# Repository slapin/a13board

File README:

Copyright (C) 2013 Sergey Lapin

These schematics and PCB layout are free: you can redistribute it
and/or modify it under the terms of the GNU General Public License
as published by the Free Software Foundation, either version 3
of the License, or (at your option) any later version.

This schematic and PCB layout are distributed in the hope that these
will be useful, but WITHOUT ANY WARRANTY; without even the implied
warranty of MERCHANTABILITY or FITNESS FOR A PARTICULAR PURPOSE.
See the GNU General Public License for more details.

You should have received a copy of the GNU General Public License
along with this program.  If not, see <http://www.gnu.org/licenses/>.

Please note, that this license is only for schematics and board layout,
and symbol libraries.
I don't know, and I don't want to know of any patent issues you can get
into using this design. Good luck.

Also, `sexpdata` is licensed under the terms of the BSD 2-Clause License.
See the source code for more information.

Symbol for Allwinner A13 was taken from Olimex PCB for OLinuXino,
and is subject to their license and permissions.
See https://github.com/OLIMEX/OLINUXINO

S.

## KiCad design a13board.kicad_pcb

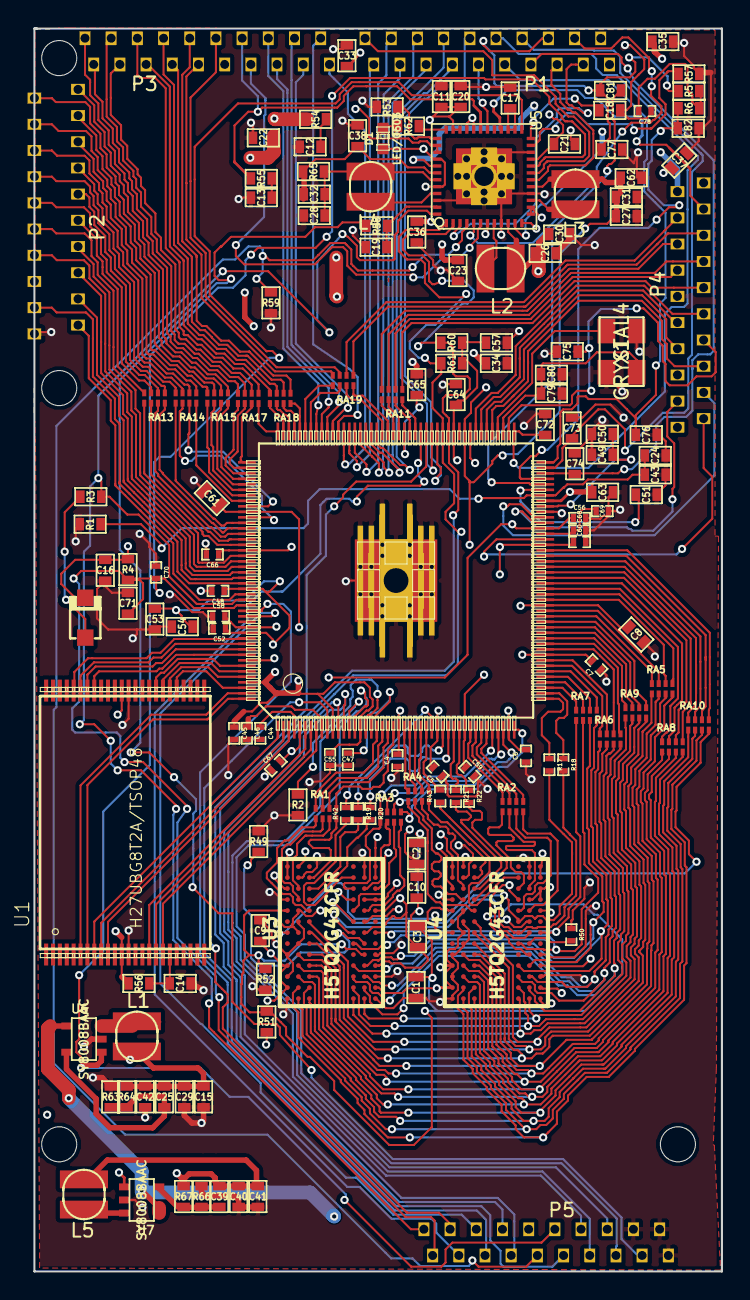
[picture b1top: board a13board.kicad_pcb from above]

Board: 4 copper layers, 50.0 x 90.4 mm, 156 parts (0 on the bottom side), 271 nets.

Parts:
1PIN, 1PIN#2, 1PIN#3, 1PIN#4: P***; 1pin
C1, C2, C3: 100nF; SM0603_Capa
C4, C5, C6, C7, C45, C47, C52, C55, C56, C60, C67, C69: 100nF; SM0402
C8, C9, C10, C15, C43, C50, C54, C57, C64, C65, C71, C81: 100nF; SM0603A
C11, C12, C13, C20, C21, C22, C23, C24, C26, C27, C28, C33, C34, C35, C36, C37, C38, C49, C53, C62, C82: 10uF/6.3V; SM0603A
C14: NA(100nF); SM0603A
C16: NA(22uF/6.3V); SM0603A
C17, C18, C32, C51: 1uF; SM0603A
C19, C30, C31, C72, C73, C74, C75, C76: 1nF; SM0603A
C25: 47pF; SM0603A
C29, C40, C41, C42, C63: 22uF/6.3V; SM0603A
C39: 22pF; SM0603A
C44, C58, C66: 22uF/6.3V; SM0402
C46, C48, C59, C68, C78: 10uF/6.3V; SM0402
C61: 100nF; SM0603
C70: 1uF; SM0402
C77: 3.3nF; SM0603A
C79, C80: 33pF; SM0603A
D1: LED/0603; LED-0603
D2: 1N5819(S4SOD-123); SOD123
L1, L2, L3, L4, L5: 2.2uH/1.5A/DCR<0.1R/CD32; CD32
P1, P2, P3, P4, P5: CONN_20; CONN20-1.27zzz
R1, R57: 200k/1%; SM0603A
R2, R49, R53: 240R/1%; SM0603A
R3, R4: 47k; SM0603A
R5, R6, R58, R59, R60, R61, R62: 2.2k; SM0603A
R17, R18, R19, R20, R21, R22, R42, R43: 22R; SM0402
R50: 240R/1%; SM0402
R51, R52: 2k/1%; SM0603A
R54, R55: 1R; SM0603A
R56: NA(10k); SM0603A
R63: 22k/1%; SM0603A
R64: 100k/1%; SM0603A
R65: 0.03R/1%; SM0603A
R66: 3.3k/1%; SM0603A
R67: 4.99k/1%; SM0603A
RA1, RA2, RA3, RA4, RA5, RA6, RA7, RA8, RA9, RA10, RA11, RA13, RA14, RA15, RA17, RA18, RA19: RA4X0402; RN4x0402
U1: H27UBG8T2A/TSOP48; TSOP48
U2: A13; allwinner_a13-OLIMEX_IC_TQFP176
U3, U4: H5TQ2G43CFR; BGA78
U5: OLIMEX_IC_AXP209; QFN48+1
U6, U7: SY8008BAAC; SOT23-5
X1: CRYSTAL4; C5032

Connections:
5V_EXT: P3.9, R54.2, U5.32, U5.33
5V_OTG: P3.8, R55.2, U5.31
+3.3V: C15.1, C16.1, C25.2, C29.2, C42.2, C56.2, C57.2, C58.1, C61.1, C64.1, C67.1, D2.1, L1.2, P4.1, R4.1, R56.1, R60.1, R61.1, R64.2, U1.12, U1.37, U2.5, U2.76, U2.97, U2.100, U2.142, U2.163
+BATT: P1.20, U5.38, U5.39
/DRAM/CPU_A0: RA5.1, U2.64
/DRAM/CPU_A1: RA6.3, U2.52
/DRAM/CPU_A2: RA8.3, U2.66
/DRAM/CPU_A3: RA8.4, U2.65
/DRAM/CPU_A4: RA6.4, U2.51
/DRAM/CPU_A5: RA8.2, U2.67
/DRAM/CPU_A6: RA6.2, U2.54
/DRAM/CPU_A7: RA10.2, U2.71
/DRAM/CPU_A8: RA6.1, U2.55
/DRAM/CPU_A9: RA10.4, U2.69
/DRAM/CPU_A10: RA7.3, U2.48
/DRAM/CPU_A11: RA9.4, U2.56
/DRAM/CPU_A12: RA7.1, U2.50
/DRAM/CPU_A13: RA8.1, U2.68
/DRAM/CPU_A14: RA9.3, U2.57
/DRAM/CPU_BA0: RA5.2, U2.63
/DRAM/CPU_BA1: RA7.2, U2.49
/DRAM/CPU_BA2: RA5.3, U2.61
/DRAM/CPU_CAS: RA9.1, U2.59
/DRAM/CPU_CK: R17.2, U2.45
/DRAM/CPU_CKE: RA7.4, U2.47
/DRAM/CPU_CK_N: R18.2, U2.46
/DRAM/CPU_D0: RA1.1, U2.22
/DRAM/CPU_D1: RA3.4, U2.40
/DRAM/CPU_D2: RA1.2, U2.21
/DRAM/CPU_D3: RA3.3, U2.41
/DRAM/CPU_D4: RA1.4, U2.19
/DRAM/CPU_D5: RA3.1, U2.44
/DRAM/CPU_D6: RA1.3, U2.20
/DRAM/CPU_D7: RA3.2, U2.42
/DRAM/CPU_D8: RA2.3, U2.37
/DRAM/CPU_D9: RA4.3, U2.25
/DRAM/CPU_D10: RA2.1, U2.39
/DRAM/CPU_D11: RA4.4, U2.24
/DRAM/CPU_D12: RA2.4, U2.36
/DRAM/CPU_D13: RA4.2, U2.26
/DRAM/CPU_D14: RA2.2, U2.38
/DRAM/CPU_D15: RA4.1, U2.27
/DRAM/CPU_DM0: R42.1, U2.29
/DRAM/CPU_DM1: R43.1, U2.28
/DRAM/CPU_DQS0: R19.2, U2.31
/DRAM/CPU_DQS0_N: R20.2, U2.32
/DRAM/CPU_DQS1: R21.2, U2.33
/DRAM/CPU_DQS1_N: R22.2, U2.34
/DRAM/CPU_MEMRST: RA10.3, U2.70
/DRAM/CPU_ODT: RA10.1, U2.72
/DRAM/CPU_RAS: RA9.2, U2.58
/DRAM/CPU_WE: RA5.4, U2.60
/DRAM/DDR3_A0: RA5.8, U3.K3, U4.K3
/DRAM/DDR3_A1: RA6.6, U3.L7, U4.L7
/DRAM/DDR3_A2: RA8.6, U3.L3, U4.L3
/DRAM/DDR3_A3: RA8.5, U3.K2, U4.K2
/DRAM/DDR3_A4: RA6.5, U3.L8, U4.L8
/DRAM/DDR3_A5: RA8.7, U3.L2, U4.L2
/DRAM/DDR3_A6: RA6.7, U3.M8, U4.M8
/DRAM/DDR3_A7: RA10.7, U3.M2, U4.M2
/DRAM/DDR3_A8: RA6.8, U3.N8, U4.N8
/DRAM/DDR3_A9: RA10.5, U3.M3, U4.M3
/DRAM/DDR3_A10: RA7.6, U3.H7, U4.H7
/DRAM/DDR3_A11: RA9.5, U3.M7, U4.M7
/DRAM/DDR3_A12: RA7.8, U3.K7, U4.K7
/DRAM/DDR3_A13: RA8.8, U3.N3, U4.N3
/DRAM/DDR3_A14: RA9.6, U3.N7, U4.N7
/DRAM/DDR3_BA0: RA5.7, U3.J2, U4.J2
/DRAM/DDR3_BA1: RA7.7, U3.K8, U4.K8
/DRAM/DDR3_BA2: RA5.6, U3.J3, U4.J3
/DRAM/DDR3_CAS: RA9.8, U3.G3, U4.G3
/DRAM/DDR3_CK: R17.1, U3.F7, U4.F7
/DRAM/DDR3_CKE: RA7.5, U3.G9, U4.G9
/DRAM/DDR3_CK_N: R18.1, U3.G7, U4.G7
/DRAM/DDR3_D0: RA1.8, U3.B3
/DRAM/DDR3_D1: RA3.5, U3.C7
/DRAM/DDR3_D2: RA1.7, U3.C2
/DRAM/DDR3_D3: RA3.6, U3.C8
/DRAM/DDR3_D4: RA1.5, U3.E3
/DRAM/DDR3_D5: RA3.8, U3.E8
/DRAM/DDR3_D6: RA1.6, U3.D2
/DRAM/DDR3_D7: RA3.7, U3.E7
/DRAM/DDR3_D8: RA2.6, U4.C8
/DRAM/DDR3_D9: RA4.6, U4.D2
/DRAM/DDR3_D10: RA2.8, U4.E8
/DRAM/DDR3_D11: RA4.5, U4.E3
/DRAM/DDR3_D12: RA2.5, U4.C7
/DRAM/DDR3_D13: RA4.7, U4.C2
/DRAM/DDR3_D14: RA2.7, U4.E7
/DRAM/DDR3_D15: RA4.8, U4.B3
/DRAM/DDR3_DM0: R42.2, U3.B7
/DRAM/DDR3_DM1: R43.2, U4.B7
/DRAM/DDR3_DQS0: R19.1, U3.C3
/DRAM/DDR3_DQS0_N: R20.1, U3.D3
/DRAM/DDR3_DQS1: R21.1, U4.C3
/DRAM/DDR3_DQS1_N: R22.1, U4.D3
/DRAM/DDR3_ODT: RA10.8, U3.G1, U4.G1
/DRAM/DDR3_RAS: RA9.7, U3.F3, U4.F3
/DRAM/DDR3_RST: RA10.6, U3.N2, U4.N2
/DRAM/DDR3_WE: RA5.5, U3.H3, U4.H3
/NAND/NALE: U1.17, U2.7
/NAND/NAND_WP: C14.1, R56.2, U1.19
/NAND/NCE0: U1.9, U2.2
/NAND/NCE1: U1.10, U2.3
/NAND/NCLE: U1.16, U2.6
/NAND/NDQ0: U1.29, U2.174
/NAND/NDQ1: U1.30, U2.172
/NAND/NDQ2: U1.31, U2.171
/NAND/NDQ3: U1.32, U2.170
/NAND/NDQ4: U1.41, U2.168
/NAND/NDQ5: U1.42, U2.167
/NAND/NDQ6: U1.43, U2.166
/NAND/NDQ7: U1.44, U2.165
/NAND/NRB0: U1.7, U2.176
/NAND/NRB1: U1.6, U2.175
/NAND/NRE: U1.8, U2.1
/NAND/NWE: U1.18, U2.8
/power/VDD_CPU: C26.2, C30.2, C44.2, C45.2, C46.2, C47.2, C48.2, C52.2, C53.2, C54.2, L2.2, U2.4, U2.9, U2.11, U2.16, U2.156, U2.164, U2.169, U2.173, U5.10
/power/VDD_INT: C27.2, C31.2, C59.2, C60.2, C62.2, C65.2, C66.2, L3.2, U2.35, U2.73, U2.98, U2.109, U2.149, U5.17
BACKUP: P1.10, U5.30
EXTEN: P5.10, U5.20, U6.1
GND: C1.2, C2.2, C4.2, C5.2, C6.2, C7.2, C8.2, C9.2, C10.2, C11.1, C12.1, C13.1, C14.2, C15.2, C16.2, C17.1, C18.1, C19.1, C20.1, C21.2, C22.2, C23.2, C24.1, C26.1, C27.1, C28.1, C29.1, C30.1, C31.1, C33.2, C34.2, C35.2, C36.2, C37.2, C38.1, C40.1, C41.1, C42.1, C43.1, C44.1, C45.1, C46.1, C47.1, C48.1, C49.1, C50.1, C51.2, C52.1, C53.1, C54.1, C55.2, C56.1, C57.1, C58.2, C59.1, C60.1, C61.2, C62.1, C63.2, C64.2, C65.1, C66.1, C67.2, C68.1, C69.1, C70.2, C71.2, C72.2, C73.2, C74.2, C75.2, C76.2, C77.2, C78.2, C79.1, C80.1, C82.2, P2.1, P4.11, P5.1, P5.2, P5.4, R1.1, R2.2, R49.2, R50.2, R52.2, R53.1, R57.1, R59.1, R63.1, R66.1, U1.13, U1.36, U2.79, U2.GND, U3.A1, U3.A8, U3.B1, U3.B2, U3.B8, U3.C9, U3.D1, U3.D8, U3.D9, U3.F2, U3.F8, U3.H2, U3.J1, U3.J9, U3.L1, U3.L9, U3.N1, U3.N9, U4.A1, U4.A8, U4.B1, U4.B2, U4.B8, U4.C9, U4.D1, U4.D8, U4.D9, U4.F2, U4.F8, U4.H2, U4.J1, U4.J9, U4.L1, U4.L9, U4.N1, U4.N9, U5.9, U5.16, U5.22, U5.46, U5.GND, U6.2, U7.2, X1.2, X1.4
HPCOM: P4.3, U2.77
HPOUTL: P4.2, U2.74
HPOUTR: P4.4, U2.78
IPSOUT: C11.2, C20.2, C21.1, C22.1, C23.1, C36.1, D1.1, P4.5, P5.12, U5.7, U5.13, U5.14, U5.21, U5.34, U5.35, U5.40, U5.44, U6.4, U7.4
LDO4_3V3_200MA: C37.1, P4.20, U5.11
LRADC: C74.1, P1.14, U2.86
MIC: C77.1, C81.1, P1.15, R5.1
unnamed: R50.1, U4.H8
unnamed: R49.1, U3.H8
unnamed: C1.1, C2.1, C3.2, C10.1, R51.2, R52.1, U3.E1, U3.J8, U4.E1, U4.J8
unnamed: L1.1, U6.3
unnamed: L5.1, U7.3
unnamed: C25.1, R63.2, R64.1, U6.5
unnamed: C39.1, R66.2, R67.1, U7.5
unnamed: C68.2, C69.2, U2.75
unnamed: D2.2, R3.1
unnamed: C32.1, C38.2, R65.2, U5.42
unnamed: C49.2, C50.2, U2.80
unnamed: C24.2, C43.2, R1.2, U2.82
unnamed: R2.1, U2.17
unnamed: C51.1, U2.83
unnamed: L3.1, U5.15
unnamed: L4.1, U5.45
unnamed: C17.2, U5.26, U5.27
unnamed: R53.2, U5.37
unnamed: L2.1, U5.8
unnamed: R62.2, U5.36
unnamed: C12.2, R54.1
unnamed: C13.2, R55.1
unnamed: D1.2, R62.1
unnamed: R57.2, U5.23
unnamed: C18.2, U5.24
unnamed: C28.2, C32.2, L4.2, R65.1, U5.43
unnamed: C19.2, R58.2, U5.47
unnamed: RA11.1, U2.111
unnamed: RA14.3, U2.141
unnamed: RA14.2, U2.143
unnamed: RA14.1, U2.144
unnamed: RA13.4, U2.145
unnamed: RA13.3, U2.146
unnamed: RA13.2, U2.147
unnamed: RA13.1, U2.148
unnamed: RA14.4, U2.140
unnamed: RA11.2, U2.110
unnamed: RA19.1, U2.127
unnamed: RA19.2, U2.126
unnamed: RA15.1, U2.139
unnamed: RA18.4, U2.128
unnamed: RA18.3, U2.129
unnamed: RA18.2, U2.130
unnamed: RA18.1, U2.131
unnamed: RA17.4, U2.132
unnamed: RA17.3, U2.133
unnamed: RA17.2, U2.134
unnamed: RA17.1, U2.135
unnamed: RA15.4, U2.136
unnamed: RA15.3, U2.137
unnamed: RA15.2, U2.138
unnamed: C79.2, C80.2, U2.91, X1.1
unnamed: RA19.3, U2.113
unnamed: RA11.4, U2.107
unnamed: RA11.3, U2.108
unnamed: RA19.4, U2.112
unnamed: C81.2, U2.84
unnamed: C78.1, R5.2, R6.1
unnamed: C82.1, R6.2, U2.85
unnamed: U2.92, X1.3
NMI_N: P5.20, R3.2, U2.158, U5.48
PB2: P1.9, U2.103
PB3: P2.9, U2.150
PB4: P1.8, U2.104
PB10: P5.9, U2.10
PB15: P5.18, U2.105
PB16: P5.17, U2.106
PB17: P5.16, U2.161
PB18: P5.15, U2.160
PD2: P2.10, RA13.8
PD3: P2.11, RA13.7
PD4: P2.12, RA13.6
PD5: P2.13, RA13.5
PD6: P2.14, RA14.8
PD7: P2.15, RA14.7
PD10: P2.16, RA14.6
PD11: P2.17, RA14.5
PD12: P2.18, RA15.8
PD13: P2.19, RA15.7
PD14: P2.20, RA15.6
PD15: P3.20, RA15.5
PD18: P3.19, RA17.8
PD19: P3.18, RA17.7
PD20: P3.17, RA17.6
PD21: P3.16, RA17.5
PD22: P3.15, RA18.8
PD23: P3.14, RA18.7
PD24: P3.13, RA18.6
PD25: P3.12, RA18.5
PD26: P3.11, RA19.8
PD27: P3.10, RA19.7
PE0: P1.7, U2.114
PE1: P1.6, U2.115
PE2: P1.5, U2.116
PE3: P1.4, U2.117
PE4: P1.3, U2.118
PE5: P1.2, U2.119
PE6: P3.1, U2.120
PE7: P3.2, U2.121
PE8: P3.3, U2.122
PE9: P3.4, U2.123
PE10: P3.5, U2.124
PE11: P3.6, U2.125
PG0: P2.3, U2.155
PG1: P2.4, U2.154
PG2: P2.6, U2.153
PG3: P2.7, U2.152
PG4: P2.8, U2.151
PG9: P5.8, U2.12
PG10: P5.7, U2.13
PG11: P5.6, U2.14
PG12: P5.5, U2.15
PIN0: P1.1, U5.19
PIN1: P1.16, U5.18
PIN2: P1.17, U5.5
PIN3: P1.18, U5.3
PWR_BUT: P5.3, R58.1
RESET: C70.1, C71.1, P5.19, R4.2, U2.159, U5.25
RESET_SW2: P5.11, R59.2, U5.4
SDC0_CLK: P4.14, RA11.7
SDC0_CMD: P4.15, RA11.8
SDC0_D0: P4.13, RA11.6
SDC0_D1: P4.12, RA11.5
SDC0_D2: P4.17, RA19.6
SDC0_D3: P4.16, RA19.5
SVREF: C55.1, U2.18
TPX1: C72.1, P1.11, U2.89
TPX2: C73.1, P1.13, U2.87
TPY1: C75.1, P4.8, U2.90
TPY2: C76.1, P1.12, U2.88
TWI0_SCK: P5.14, R60.2, U2.101, U5.2
TWI0_SDA: P5.13, R61.2, U2.102, U5.1
UBOOT: P2.2, U2.157
USB0-DRV: P3.7, U5.6
USB_UDM0: P4.6, U2.93
USB_UDM1: P4.9, U2.95
USB_UDP0: P4.7, U2.94
USB_UDP1: P4.10, U2.96
VDD_RTC: C33.1, P4.18, U5.28
VMEM: C3.1, C4.1, C5.1, C6.1, C7.1, C8.1, C9.1, C39.2, C40.2, C41.2, L5.2, R51.1, R67.2, U2.23, U2.30, U2.43, U2.53, U2.62, U3.A2, U3.A9, U3.B9, U3.C1, U3.D7, U3.E2, U3.E9, U3.G2, U3.G8, U3.K1, U3.K9, U3.M1, U3.M9, U4.A2, U4.A9, U4.B9, U4.C1, U4.D7, U4.E2, U4.E9, U4.G2, U4.G8, U4.K1, U4.K9, U4.M1, U4.M9
VPP: C34.1, C63.1, P2.5, U2.81, U5.12, U7.1
WIFI-3V3: C35.1, P4.19, U5.41

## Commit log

2013-03-19 Added axp209 module
2013-03-19 Better pin placement
2013-03-19 Some more pin names
2013-03-19 added some schematics
2013-03-19 added dcm file
2013-03-19 added hynix library
2013-03-19 added tsop48
2013-03-20 Started drawing
2013-03-20 Added more libraries; more advancement
2013-03-20 still ERC errors
2013-03-21 Proper laying out DDR3 in schematics
2013-03-22 DDR3 is mostly captured
2013-03-24 Finished DRAM, started power
2013-03-25 Power update; started CPU
2013-03-25 Fixed values for inductors
2013-03-26 added 3.3V power supply
2013-03-26 added resistor arrays, continue routing main CPU
2013-03-27 added schematic PDF
2013-03-27 Re-made A13 power part, finished power schematics
2013-03-28 Finished schematics, now fixing errors
2013-03-28 Generated CPU pdf
2013-03-28 Added forgotten connectors.sch
2013-03-28 Added .gitignore
2013-03-28 Added diode footprint
2013-03-28 Added ad-hoc BGA78 for memory
2013-03-28 dcm for ax209
2013-03-28 new BGA78 module
2013-03-28 Fixing schematics bugs
2013-03-28 Started making board and modules
2013-03-29 fixed schematics errors, added CD32 and 4x0402 packages, started layout
2013-03-29 Started tracing
2013-03-31 more tracing progress
2013-03-31 manufacturers data
2013-04-01 Adding gerber files
2013-04-02 Re-tracing DDR3 with 4mil traces
2013-04-03 Added dxf files
2013-04-03 still routing ddr3
2013-04-04 Routed ground poly and most of ddr3
2013-04-04 more routing of DDR3
2013-04-05 more routing of ddr3, found smaller approach, bga-escaping VMEM and GND
2013-04-05 reducing space, occupied by address lines
2013-04-06 Fixed some bugs with symbols, tracing continued
2013-04-06 Added connectors
2013-04-07 Meeting 5x10 goal
2013-04-08 A bit more of tracing of PCB
2013-04-08 a bit improved layout
2013-04-08 New gerber
2013-04-08 Almost all escaped from BGA
2013-04-09 Connected a few more connections; BGA escape finished
2013-04-09 Some more traces (for connectors)
2013-04-09 Better naming for gerbers
2013-04-09 new gerbers
2013-04-09 Fixed thermal pad on A10
2013-04-09 Removed unneeded file
2013-04-09 shiny new gerbers, fixed paste and mask
2013-04-10 Added thermal for AXP209
2013-04-10 Added better stencil support
2013-04-10 Added missing footprints
2013-04-10 Added layout .png file
2013-04-10 Added bigger picture
2013-04-10 Added pic generation and automatic zip
2013-04-10 Added gerbv project file
2013-04-10 Rearranged pins so to make tracing easier
2013-04-10 Using proper module for crystal, some rearrangements regarding connectors
2013-04-10 Newer image
2013-04-11 Experimented with autotracer
2013-04-11 Different layout for connectors
2013-04-11 Proper GND fill of thermal pad on AXP209
2013-04-15 More power traced
2013-04-15 Added new crystal, changed 2 pins on connectors
2013-04-16 Almost finished tracing
2013-04-16 New gerbers and board image
2013-04-16 A few untraced connections left
2013-04-16 All traces traced...
2013-04-16 New gerber and png file
2013-04-16 Updated to people's suggestions
2013-04-16 Updated to proper zone fill
2013-04-17 Updated layout with people's suggestions
2013-04-18 Changed thermal a bit
2013-04-18 Used polygon for power pins
2013-04-18 Included all layers to gerber project, improved .png
2013-04-18 Made even better .png
2013-04-18 Added license terms
2013-04-18 Added README
2013-04-19 Fixed some power issues
2013-04-19 A little fit of border clearance fixed
2013-04-19 updated README wih terms for sexpdata.py
2013-04-19 Added sexpdata for s-expression parsing
2013-04-19 Initial script for calculating net sizes
2013-04-19 Parsing segments and nets
2013-04-20 Calculating net size
2013-04-20 Added new gerber files and png
2013-04-20 Improved data lines
2013-04-21 Fixed some symbols, hidden some silk
2013-04-21 Added proper gerber layers, fixed .dri file, some fixes of silk
2013-04-22 Updated for paste
2013-04-22 Fixed stencil apertures
2013-04-22 Fixed stencil apertures (gerbers)
2013-04-22 Added .png
2013-04-25 testing 0.12 tracks (4.7 mil)
2013-07-02 Added BOM
2013-07-02 Added BOM pdf
2014-05-16 Layout improvements, NPTH holes
